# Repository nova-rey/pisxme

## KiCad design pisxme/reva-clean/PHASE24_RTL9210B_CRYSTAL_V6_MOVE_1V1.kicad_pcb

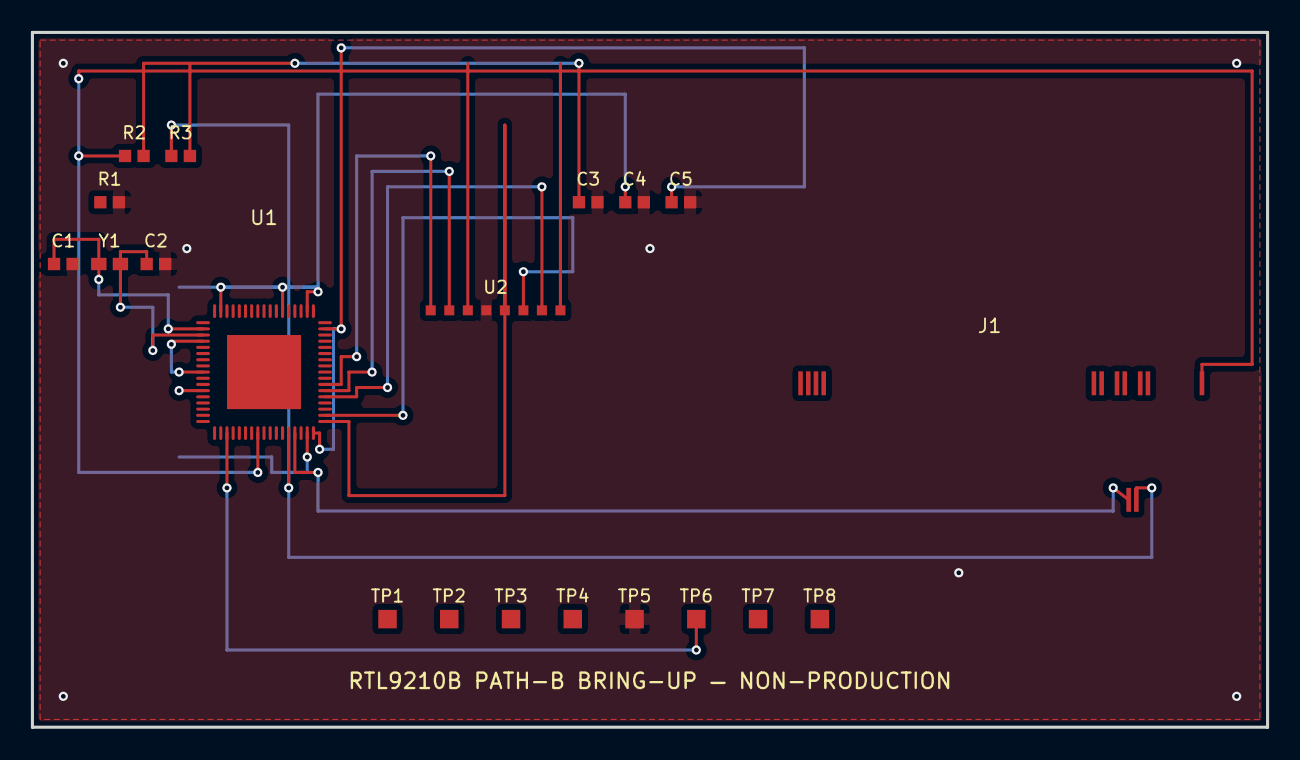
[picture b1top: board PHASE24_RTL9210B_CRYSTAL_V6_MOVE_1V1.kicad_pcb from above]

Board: 6 copper layers, 80.0 x 45.0 mm, 20 parts (0 on the bottom side), 23 nets.

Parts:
C1: 16pF_XTAL_IN; BRINGUP_16pF_XTAL_IN
C2: 16pF_XTAL_OUT; BRINGUP_16pF_XTAL_OUT
C3: RTL_3V3_DEC; BRINGUP_RTL_3V3_DEC
C4: RTL_1V1_DEC; BRINGUP_RTL_1V1_DEC
C5: RTL_5V_DEC; BRINGUP_RTL_5V_DEC
J1: M.2 Socket 3 M-key 2280; BRINGUP_M2_MKEY
R1: 12k_RSET; BRINGUP_12k_RSET
R2: PEDET_PULLUP; BRINGUP_PEDET_PULLUP
R3: CLKREQ_PULLUP; BRINGUP_CLKREQ_PULLUP
TP1: SPI_PROGRAM_CS; BRINGUP_SPI_PROGRAM_CS
TP2: SPI_PROGRAM_CLK; BRINGUP_SPI_PROGRAM_CLK
TP3: SPI_PROGRAM_SI; BRINGUP_SPI_PROGRAM_SI
TP4: SPI_PROGRAM_SO; BRINGUP_SPI_PROGRAM_SO
TP5: GND_TEST; BRINGUP_GND_TEST
TP6: RESET_TEST; BRINGUP_RESET_TEST
TP7: UART_TX_TEST; BRINGUP_UART_TX_TEST
TP8: UART_RX_TEST; BRINGUP_UART_RX_TEST
U1: RTL9210B-CG; RTL9210B-CG_QUALIFICATION
U2: W25Q128_SPI_FLASH; BRINGUP_W25Q128_SPI_FLASH
Y1: XTAL_25MHz; BRINGUP_XTAL_25MHz

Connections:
CLKREQ_N: J1.52, R3.1, U1.13
GND: C1.2, C2.2, C3.2, C4.2, C5.2, R1.2, TP5.1, U1.45, U1.66, U1.69, U2.4
LANE0_RXN: J1.41, U1.65
LANE0_RXP: J1.43, U1.64
LANE0_TXN: J1.47, U1.67
LANE0_TXP: J1.49, U1.68
PEDET: J1.69, R2.1, U1.8
PERST_N: J1.50, U1.14
REFCLK_N: J1.53, U1.62
REFCLK_P: J1.55, U1.61
RESET_N: TP6.1, U1.3
RSET: R1.1, U1.51
RTL_1V1: C4.1, U1.16, U1.25, U1.36, U1.40, U1.50, U1.55, U1.60, U1.63
RTL_3V3: C3.1, R2.2, R3.2, U1.20, U1.34, U1.39, U1.52, U2.3, U2.8
RTL_5V: C5.1, U1.17, U1.33
SPICLK: TP2.1, U1.19, U2.6
SPICS: TP1.1, U1.24, U2.1
SPISI: TP3.1, U1.18, U2.5
SPISO: TP4.1, U1.23, U2.2
SPISO3: U1.22, U2.7
SSD_3V3: J1.2, J1.4, J1.6, J1.8
XTAL_IN: C1.1, U1.53, Y1.1
XTAL_OUT: C2.1, U1.54, Y1.2

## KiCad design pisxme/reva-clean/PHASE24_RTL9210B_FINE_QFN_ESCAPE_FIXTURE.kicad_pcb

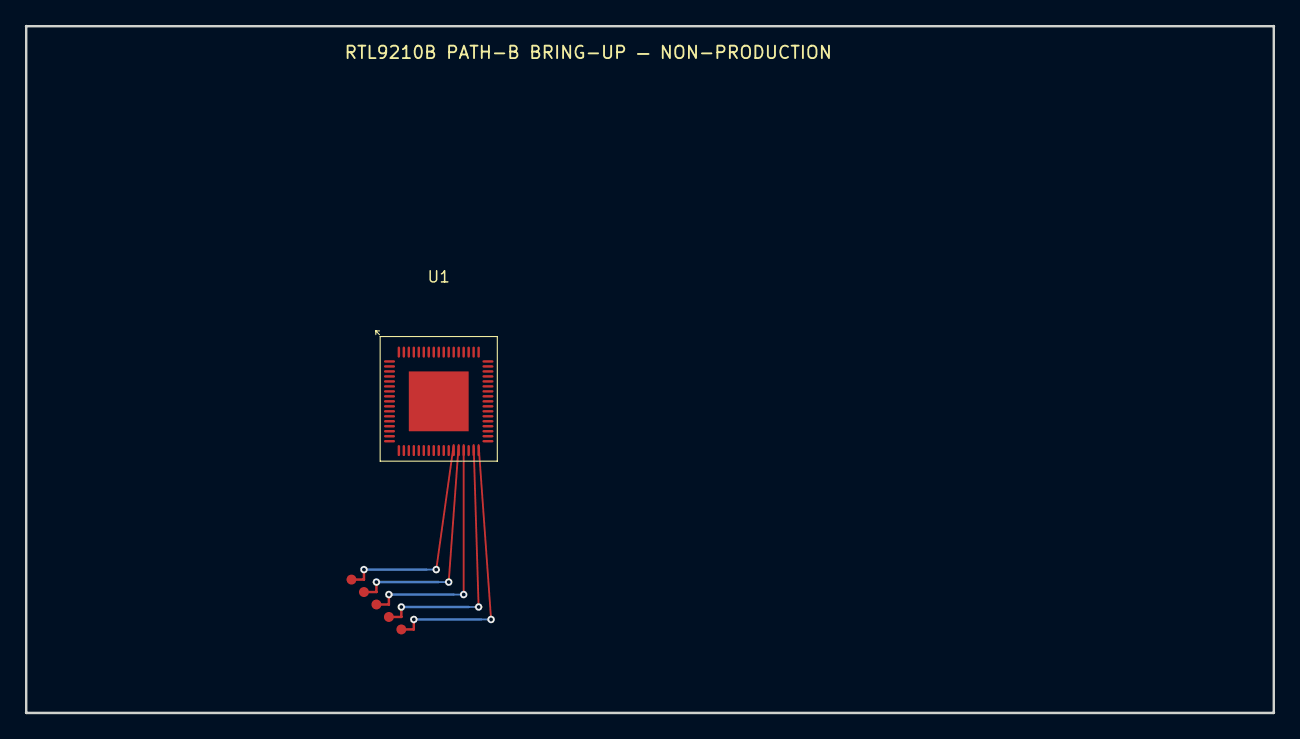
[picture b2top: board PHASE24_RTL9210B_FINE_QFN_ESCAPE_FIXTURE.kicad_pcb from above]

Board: 6 copper layers, 100.1 x 55.1 mm, 6 parts (0 on the bottom side), 5 nets.

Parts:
FQ_CLKREQ_N: CLKREQ_N_NORMAL_HANDOFF
FQ_ISOLATEB: ISOLATEB_NORMAL_HANDOFF
FQ_PERST_N: PERST_N_NORMAL_HANDOFF
FQ_RTL_1V1: RTL_1V1_NORMAL_HANDOFF
FQ_RTL_5V: RTL_5V_NORMAL_HANDOFF
U1: RTL9210B-CG; RTL9210B-CG_QUALIFICATION

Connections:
CLKREQ_N: FQ_CLKREQ_N.1, U1.13
ISOLATEB: FQ_ISOLATEB.1, U1.12
PERST_N: FQ_PERST_N.1, U1.14
RTL_1V1: FQ_RTL_1V1.1, U1.16
RTL_5V: FQ_RTL_5V.1, U1.17
